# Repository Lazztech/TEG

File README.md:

# TEG — Thermal Energy Harvesting Prototype

Electronics for a thermal energy harvesting prototype: a small TEG array feeds a
sub-1 V energy-harvesting front-end (BQ25504), which charges a buffer capacitor and backs
up a regulated 5 V rail for a Noctua 5 V PWM fan and a test load.

Originally drafted on **Flux.ai**; this repo is the **KiCad** continuation, prepared for
**JLCPCB — made and assembled**.

> **Status: the sub-watt board is complete, routed, DRC-clean and orderable — but it is now a
> REFERENCE, not the deliverable.** [REQUIREMENTS.md](REQUIREMENTS.md) re-scopes the project to a
> **fireplace-mounted, wedge-shaped harvester producing ~3–4 W** with USB-A and USB-C output. At
> ~3–4 W the BQ25504 (max input power ≤ 300 mW) cannot be used, so a new power board is in design.

## Decisions made (and why)

Settled — nothing here needs your input.

| Question | Decision | Why |
|----------|----------|-----|
| **Storage: battery or supercap?** | **Neither** — a **1000 µF electrolytic buffer** (option D) | JLCPCB stocks **no** supercapacitors and no batteries (verified against their API), so those can't be machine-assembled. An electrolytic keeps the board **100 % JLCPCB-assembled**. Trade-off accepted: ≈5 mJ stored, so the **fan runs only on live harvest**, not from storage |
| **MPPT?** | **Yes — built into the BQ25504** | Sample-and-hold MPPT in hardware; no extra IC, no firmware |
| **MPPT ratio** | **≈50 % of Voc** (`R13` = `R14` = 10 MΩ) | A TEG makes maximum power at a matched load, ≈50 % of its open-circuit voltage. The datasheet's 78 % default is tuned for *solar* |
| **Voltage window** | **VBAT_OV 3.15 V** (datasheet-verified) | Conservative and tested. Protects the part; tune later if you want more usable energy |
| **Charge cutoff** | `OT_PROG` → GND = **65 °C** | Sensible protection for a device that is warm by design |
| **`VBAT_OK`** | Left unconnected (no-connect marker) | With no real energy store, gating the load buys little. Wiring it to the MT3608 `EN` is the natural upgrade if you later add a supercap |

## Remaining tasks — from here to a working prototype

| # | Task | Notes |
|---|------|-------|
| 1 | ~~Route the copper~~ | **Done** — FreeRouting, 0 DRC violations |
| 2 | ~~Export fab files~~ | **Done** — gerbers, drill, position, BOM in `build/fab/` (verify CPL rotations) |
| 3 | **Review and order** | Read `build/fab/TEG-routed.pdf` and confirm the layout; then order from JLCPCB. ⚠️ `U1` `BQ25504RGTT` stock is only **7** — `C2876746` is the same part if it sells out |
| 4 | **Optional: add a GND pour** | GND is routed as traces so the board works as-is. A pour is a nice refinement — fill it in KiCad (**zones can't be filled from the CLI**) |
| 5 | **Bench-verify before trusting the TEGs** | Drive the input from a bench supply emulating the TEG (start ~1 V, low current limit); confirm the rail comes up and the fan starts |
| 6 | **Then the thermal tests** | One-module baseline, two-module comparison, five cold starts, 0.5 W load — per [PLAN.md](PLAN.md) |

## Routing — done with FreeRouting

KiCad has no autorouter, so routing uses the standard **SPECCTRA round-trip**, scripted in
[scripts/freeroute.sh](scripts/freeroute.sh):

1. KiCad (`pcbnew` python) exports the board as a **`.dsn`** — outline, pads, nets **and the
   net-class rules**.
2. **FreeRouting** (external Java autorouter) routes it and writes a **`.ses`** session file.
3. KiCad imports the `.ses` back onto the board.
4. `kicad-cli` DRC verifies the result.

FreeRouting reported *0 unrouted, 0 violations* on both its routing and optimisation passes,
and KiCad's own DRC agrees: **0 violations, 0 unconnected**. (It also does the rip-up-and-retry
that a naive router can't — an earlier hand-written script in `scripts/route_board.py` reached
~95 % but never clean, so it was abandoned; it's kept for reference.)

### Net classes

Set in [scripts/gen_board.py](scripts/gen_board.py) and exported into the DSN so the router
obeys them:

| Class | Nets | Track | Clearance | Via |
|-------|------|-------|-----------|-----|
| Default | all signals | 0.20 mm | 0.20 mm | 0.6/0.3 |
| Power | `GND`, `+5V`, `VSTOR`, `VBAT`, `TEG+`, `TEG-` | 0.20 mm | 0.20 mm | 0.6/0.3 |

**Why not wider power traces?** Net classes are per-*net*, and the power/GND nets also land on
U1's 0.5 mm-pitch pins, where a wider track cannot escape (0.3 mm already collides with
neighbours) and the autorouter will not taper. At tens of mA, 0.2 mm is electrically ample.
The classes still exist so wider widths can be set later, after a manual fanout from U1.

## Fabrication outputs

Generated into `build/fab/` (gitignored) by **[scripts/fab_export.sh](scripts/fab_export.sh)**
— one command for the whole JLCPCB package (Gerbers + drill + BOM + CPL). Full flow and
the ordering/approval path: **[docs/jlcpcb-fabrication.md](docs/jlcpcb-fabrication.md)**.

| File | What |
|------|------|
| `TEG-gerbers.zip` | JLCPCB PCB upload — Gerbers + drill + `.gbrjob` |
| `TEG-*.gbl/.gtl/.gbs/.gts/.gbo/.gto/.gm1` + `TEG-job.gbrjob` | Gerbers (2 copper, 2 mask, 2 silk, edge) |
| `TEG.drl` | Excellon drill |
| `TEG-pos.csv` | Raw pick-and-place (`kicad-cli pcb export pos`) |
| `TEG-CPL-jlcpcb.csv` | JLCPCB **CPL** — `Designator,Val,Package,Mid X,Mid Y,Rotation,Layer` |
| `TEG-BOM-jlcpcb.csv` | JLCPCB BOM — `Comment,Designator,Footprint,LCSC Part #` |
| `TEG-routed.pdf`, `TEG-schematic.pdf` | 2D renders for review (copper visible here) |
| `build/render/TEG-*.png` | **3D renders** (top / isometric / bottom / harvester close-up) — see [scripts/render.sh](scripts/render.sh) |

⚠️ **Check the CPL rotations before ordering.** Position-file rotation conventions are a classic
source of misplacement; compare `TEG-pos.csv` against KiCad's **Fabrication Toolkit** output (or
JLCPCB's plugin) rather than trusting it blind.

## Storage — what option D means

The BQ25504 needs some reservoir on `VBAT` (the datasheet's own reference shows ">100 µF"),
and a **1000 µF 6.3 V SMD electrolytic (`C970711`)** satisfies that: it holds the rail steady
and is placed by JLCPCB.

But it stores **≈5 mJ**, against ≈1.2 J for a supercapacitor. So:

- **The fan cannot run from storage** — it turns only while the TEG array supplies enough power
  directly (high ΔT). That is arguably the most *informative* first-prototype behaviour, but
  "fan runs for a few seconds off stored energy" is **not** a capability of this build.
- ⚠️ The electrolytic is **polarised**: pin 1 = +. **Verify against the footprint silkscreen.**

If you later want real storage, it's a one-part change: add a 0.22–0.47 F / 5.5 V supercap in
place of `C2` (hand-solder or via a 2-pin header), and optionally gate the MT3608 `EN` from
`VBAT_OK`. The threshold network already suits a 5.5 V cell.

## Parts — all verified in the JLCPCB catalogue

Sourced with [scripts/jlc_lookup.py](scripts/jlc_lookup.py) (JLCPCB's own parts API: id,
library type, stock). Highlights:

| Ref | Part | LCSC | Stock |
|-----|------|------|-------|
| `U1` | BQ25504RGTT (harvester + MPPT) | C157471 | ⚠️ 7 (alt `C2876746` = 21) |
| `U2` | MT3608 (5 V boost) | C84817 | 129 k |
| `Q1` / `D1`,`D2` | AO3400A / 1N5819WS | C20917 / C191023 | base parts |
| `L1`,`L2` | 22 µH `SWPA4020S220MT` | C82401 | 6 007 |
| `C2` | 1000 µF 6.3 V electrolytic | C970711 | 1 888 |
| `R1`/`R2`/`R3`/`R4`+`R15`/`R7`/`R6` | 5.90 / 4.02 / 5.60 / 4.42 / 4.22 / 1.43 MΩ | C2076902 / C137708 / C23190 / C166806 / C166807 / C166898 | 775 – 58 k |
| `R8` / `R9` | 73.2 kΩ / 10 kΩ (MT3608 → **5.0 V**) | C2933257 / C25804 | ok |
| `R10` / `R13`,`R14` | 1 kΩ / 10 MΩ | C21190 / C114606 | ok |
| `J1`,`J3` / `J2` | KF128 screw terminal / 4-pin fan header | C474952 / C2691448 | ok |

## Connectors & wiring

| Ref | Type | Pins | Purpose |
|-----|------|------|---------|
| **J1** | 2-pos screw terminal (`KF128-5.08-2P`) | 1: `TEG+`, 2: `TEG-` | **TEG array input** |
| **J2** | 4-pin header, 2.54 mm | 1: `GND`, 2: `+5V`, 3: `FAN_TACH`, 4: `FAN_PWM` | Noctua fan |
| **J3** | 2-pos screw terminal (`KF128-5.08-2P`) | 1: `LOAD_SW` (switched), 2: `+5V` | 5 V test load, switched by Q1 |

### Wiring two TEGs in series (current 2-position J1)

```
TEG A(-) ──┬── TEG B(+)          # series junction, made off-board in the wiring
           │
TEG A(+) ──┴── J1 pin 1  (TEG+)
TEG B(-) ────── J1 pin 2  (TEG-)
```

**Series doubles the voltage and leaves the current unchanged** — which is what you want at
low ΔT, where each module produces only a fraction of a volt. Parallel would double the current
at the same low voltage instead.

⚠️ **Limitation of the 2-position terminal:** the series junction is made in the wiring, so the
two modules **cannot be measured independently at the board**, and running the one-module
baseline means rewiring the string. The plan asks to keep module leads accessible for
independent measurement. A **3-position** terminal (`KF128-5.08-3P`, LCSC `C474953`, in stock)
would bring the midpoint onto the board — `TEG_A+`, `midpoint`, `TEG_B-` — making each module
meterable and the baseline a no-rewire change. Roughly 5 mm wider, so it needs a placement
nudge and a reroute.

### Fan

There is **no MCU on the board**, so `FAN_PWM` (J2 pin 4) must be driven by an external source —
a bench supply, signal generator, or your instrumentation. `FAN_TACH` (pin 3) has a 10 kΩ
pull-up to `+5V` (R11) so you can read fan speed. Feed the fan from `+5V` (pin 2) and `GND` (pin 1).

## Continuous validation

Every pull request runs these checks (see **[docs/validation.md](docs/validation.md)**):

| Check | What it proves |
|-------|----------------|
| **CAD artifacts** | Rebuilds the build123d wedge and requires the committed STEP/STL to match. Every STL is a closed, single-body, bed-fitting mesh. |
| **ERC / DRC** | `kicad-cli` (KiCad 10) finds no error-level schematic or board violations. |
| **Fab package** | Gerbers, drill, CPL, BOM and the JLCPCB zip build; nothing is ordered. |
| **Scripts** | All shell scripts parse and all Python sources compile. |

Run the same checks locally with `scripts/validate.sh` (add `--cad` if KiCad is
not installed). A failing CAD check usually means the committed exports are
stale: run `scripts/cad-run.sh` and commit the updated artifacts.

## What to expect when you test

**Two TG12-4 modules produce only a few hundred mW at useful ΔT, while the fan draws
~0.5 W.** With option D there is no energy store, so the fan will turn **only while ΔT is
high enough** — it will not run continuously, and it will not run from stored energy. That is
the expected behaviour of this build, not a fault.

## Repo layout

| Path | What it is |
|------|------------|
| [REQUIREMENTS.md](REQUIREMENTS.md) | **Whole-device requirements** — electrical, mechanical, thermal/safety, manufacturing, and the system BOM split into *from JLCPCB* vs *buy separately* |
| [BOM.md](BOM.md) | Board bill of materials (the sub-watt reference design) |
| [PLAN.md](PLAN.md) | Living plan: findings, decisions, open questions, changelog |
| [docs/validation.md](docs/validation.md) | **CI + local validation flow** — what every push checks, how to fix a failing artifact |
| [.github/workflows/validate.yml](.github/workflows/validate.yml) | CI: rebuild/validate CAD, lint/test the model code, run KiCad ERC/DRC, syntax-check scripts |
| [docs/jlcpcb-fabrication.md](docs/jlcpcb-fabrication.md) | **End-to-end JLCPCB flow** — fab package command, verification checklist, manual approval-gated ordering |
| `hardware/TEG.kicad_pro` | KiCad project |
| `hardware/TEG.kicad_sch` | Root schematic (auto-generated — nets defined by pin labels) |
| `hardware/TEG.kicad_pcb` | Board (auto-generated — 33 footprints placed and netted, **no copper routed yet**) |
| `hardware/libs/TEG.kicad_sym` | Project symbol library (`TEG:`) |
| `hardware/footprints/TEG.pretty/` | Project footprint library (`TEG:`) |
| `hardware/easyeda2kicad.3dshapes/` | 3D WRL models, named as the footprints reference them |
| `scripts/gen_schematic.py` | Regenerates `TEG.kicad_sch` from the part/net table inside it |
| `scripts/gen_board.py` | Regenerates `TEG.kicad_pcb` (shares the netlist with `gen_schematic.py`) |
| `scripts/validate.sh` | **All checks**: rebuild/validate the code-CAD exports, then KiCad ERC + DRC (`--cad` / `--hardware` for one half) |
| `scripts/validate_cad.py` | Validates committed CAD STEP/STL artifacts: manifold mesh, bed fit, STEP↔STL agreement, stale-export check |
| `scripts/jlc_lookup.py` | Queries JLCPCB's own parts API — id, library type, stock |
| `scripts/fab_export.sh` | **One command** → JLCPCB package (Gerbers + drill + BOM + CPL) in `build/fab/` |
| `scripts/jlc_bom.py` | Schematic → JLCPCB BOM CSV (`Comment,Designator,Footprint,LCSC Part #`) |
| `scripts/jlc_cpl.py` | KiCad `pos` CSV → JLCPCB CPL CSV |
| `scripts/freeroute.sh` | Routes the board via the SPECCTRA DSN→FreeRouting→SES round-trip, then DRCs |
| `scripts/render.sh` | Renders 3D views of the board (with component bodies) into `build/render/` |
| `scripts/route_board.py` | *Abandoned* hand-written router (kept for reference; not used) |

## Opening the project

Open `hardware/TEG.kicad_pro` in **KiCad 7 or 8** (developed with KiCad 10). The library
tables are already set up, so all parts appear under the `TEG:` nickname.

The schematic and board are **generated** — edit the part/net table in
`scripts/gen_schematic.py` (and placements in `scripts/gen_board.py`) and re-run:

```bash
python3 scripts/gen_schematic.py   # -> hardware/TEG.kicad_sch
python3 scripts/gen_board.py       # -> hardware/TEG.kicad_pcb (unrouted, wipes routing)
./scripts/freeroute.sh             # route it (DSN -> FreeRouting -> SES -> DRC)
./scripts/validate.sh              # all checks (CAD artifacts + ERC/DRC)
./scripts/validate.sh --cad        # CAD artifacts only, no KiCad needed
python3 scripts/jlc_lookup.py "22uH inductor"   # search the JLCPCB catalogue

# one-command JLCPCB package: gerbers + drill + BOM + CPL into build/fab/
scripts/fab_export.sh              # see docs/jlcpcb-fabrication.md (ordering is manual + approval-gated)
```

**Known cosmetic warnings** (safe to ignore): ERC reports 3 × `lib_symbol_mismatch` on the two
most recently fetched symbols (their embedded text is byte-identical to the library — an
unresolved KiCad quirk), and DRC reports 1 × `silk_overlap` where the 8 mm electrolytic's
reference text crosses its own silkscreen. Neither affects fabrication.

## Tooling — JLCPCB parts

Two tools, for different jobs:

- **`scripts/jlc_lookup.py`** — *finding* parts. Queries JLCPCB's own API and returns id,
  library type (`base` = no setup fee / `expand` = extended) and stock.
- **`jlc-client`** — *fetching* a part's KiCad symbol/footprint/3D model by LCSC id, and
  appending symbols to the project library:

```bash
# Fetch symbol + footprint + 3D and append the symbol to the project library
JLC_API_TOKEN='<token>' jlc-client --symbol -l ./hardware/libs/TEG.kicad_sym \
    --footprint --footprint-lib TEG -o ./hardware/footprints C157471 C84817
```

Caveats learned the hard way (see [PLAN.md](PLAN.md) §3):

- `jlc-client`'s **search** is unreliable — as of 2026-10-10 it returns the same high-stock
  list for *every* query. Use `jlc_lookup.py` to search and `jlc-client` to fetch by id.
- `jlc-client search --type ic` also filters to one subcategory and hides power ICs.
- The component **fetch** endpoint is intermittent (`Component … not found on EasyEDA/LCSC`
  for everything, then recovers). Retry.

## Design in one paragraph

Two Marlow TG12-4-01LS TEG modules in series feed the BQ25504 boost charger through a screw
terminal. The BQ25504 does **MPPT in hardware**: `R13`/`R14` sample a fraction of the
harvester's open-circuit voltage onto a hold cap, and the chip regulates its input to that
fraction — set to **≈50 % of Voc**, matched-load MPP for a TEG. The charger holds a 1000 µF
electrolytic buffer on `VBAT` and exposes `VSTOR`; an MT3608 boost then regulates a 5 V rail
for the Noctua NF-A8 4-pin PWM fan (Tach pull-up, PWM from a test header) and a switchable
0.5 W test load (AO3400A low-side MOSFET). Two-stage on purpose: it keeps the harvester's MPPT
decoupled from load transients and lets the buffer stabilise before the 5 V boost is asked to run.

Open questions and thermal/mechanical context: [PLAN.md](PLAN.md).

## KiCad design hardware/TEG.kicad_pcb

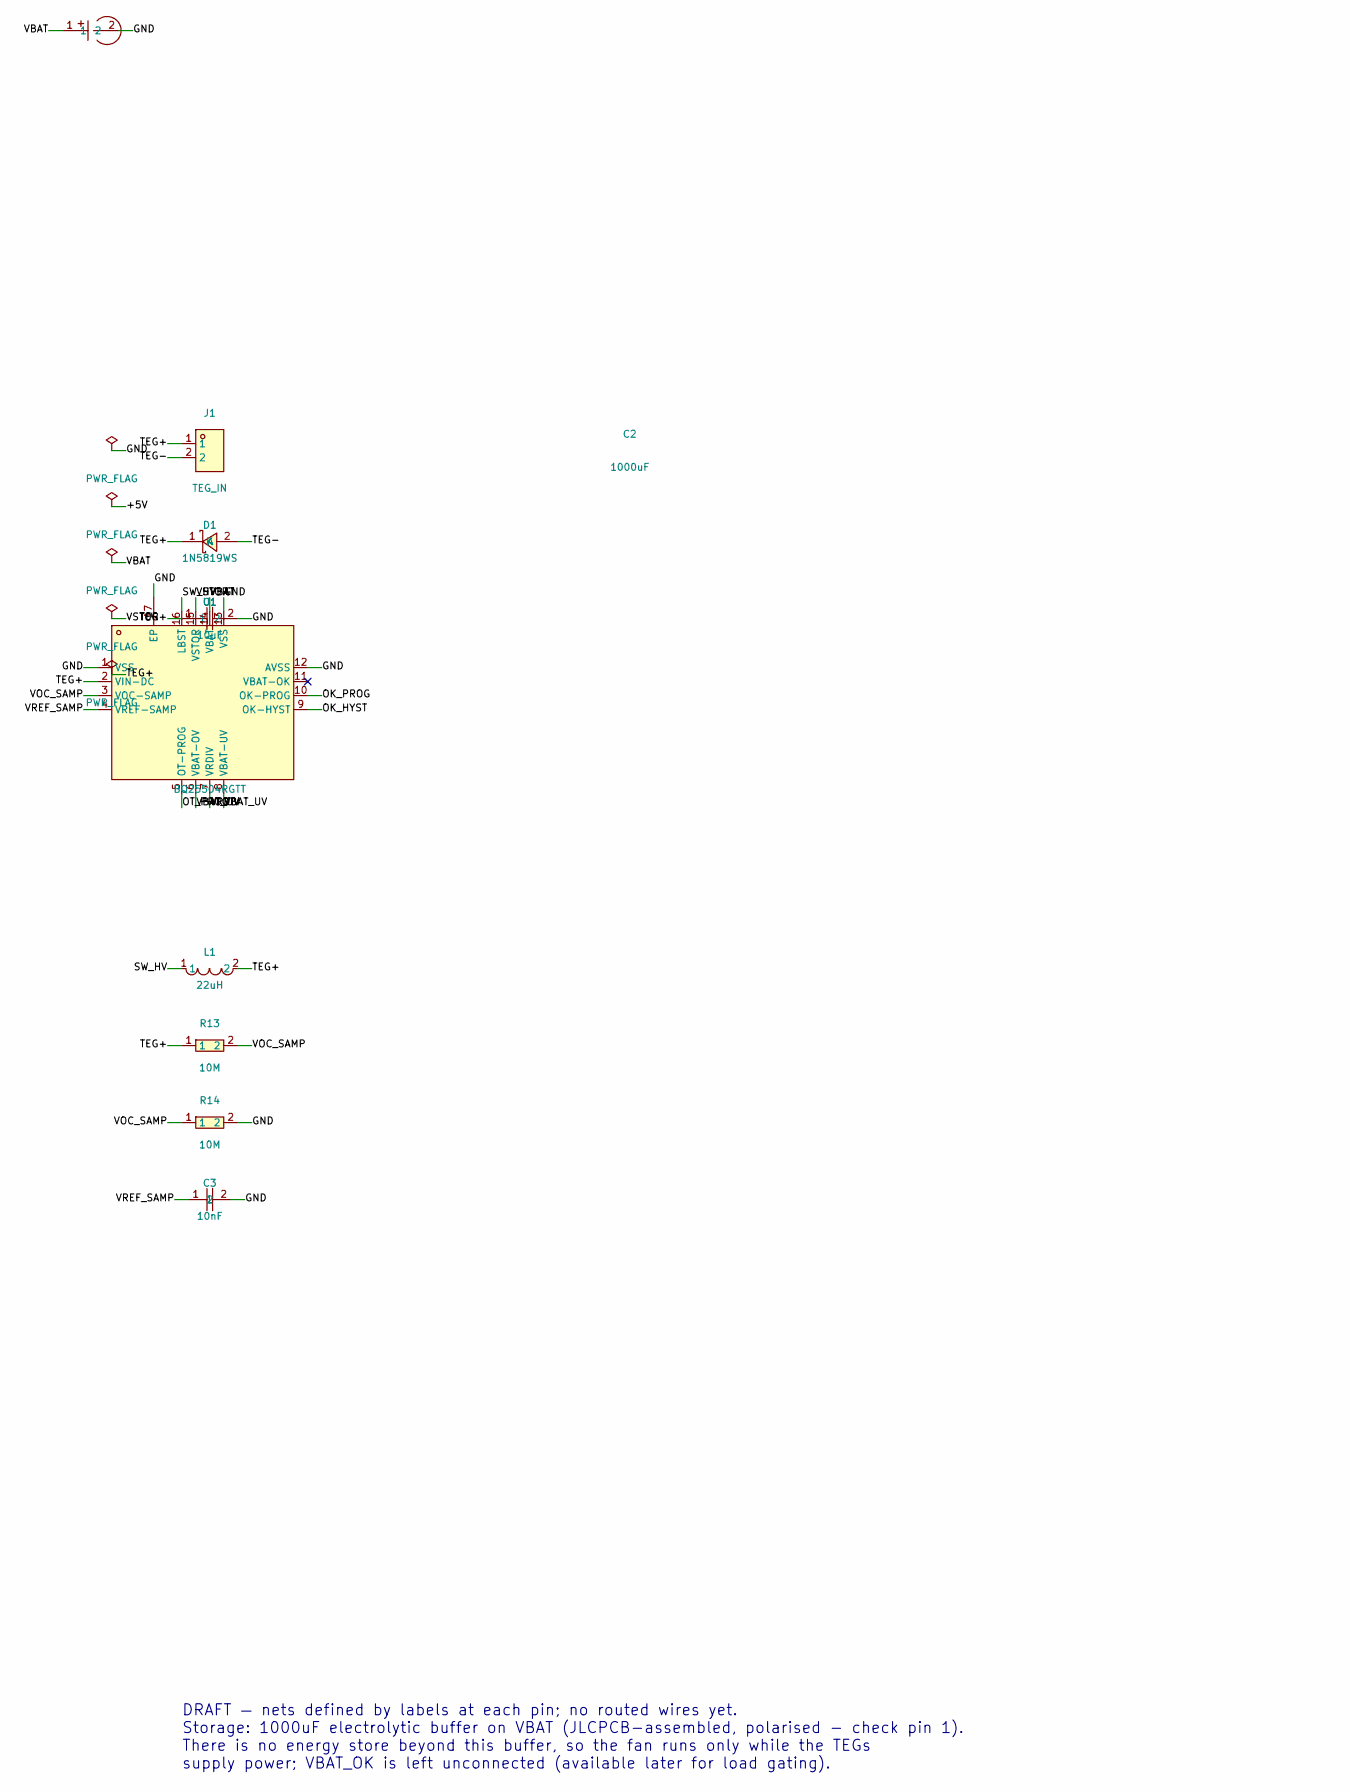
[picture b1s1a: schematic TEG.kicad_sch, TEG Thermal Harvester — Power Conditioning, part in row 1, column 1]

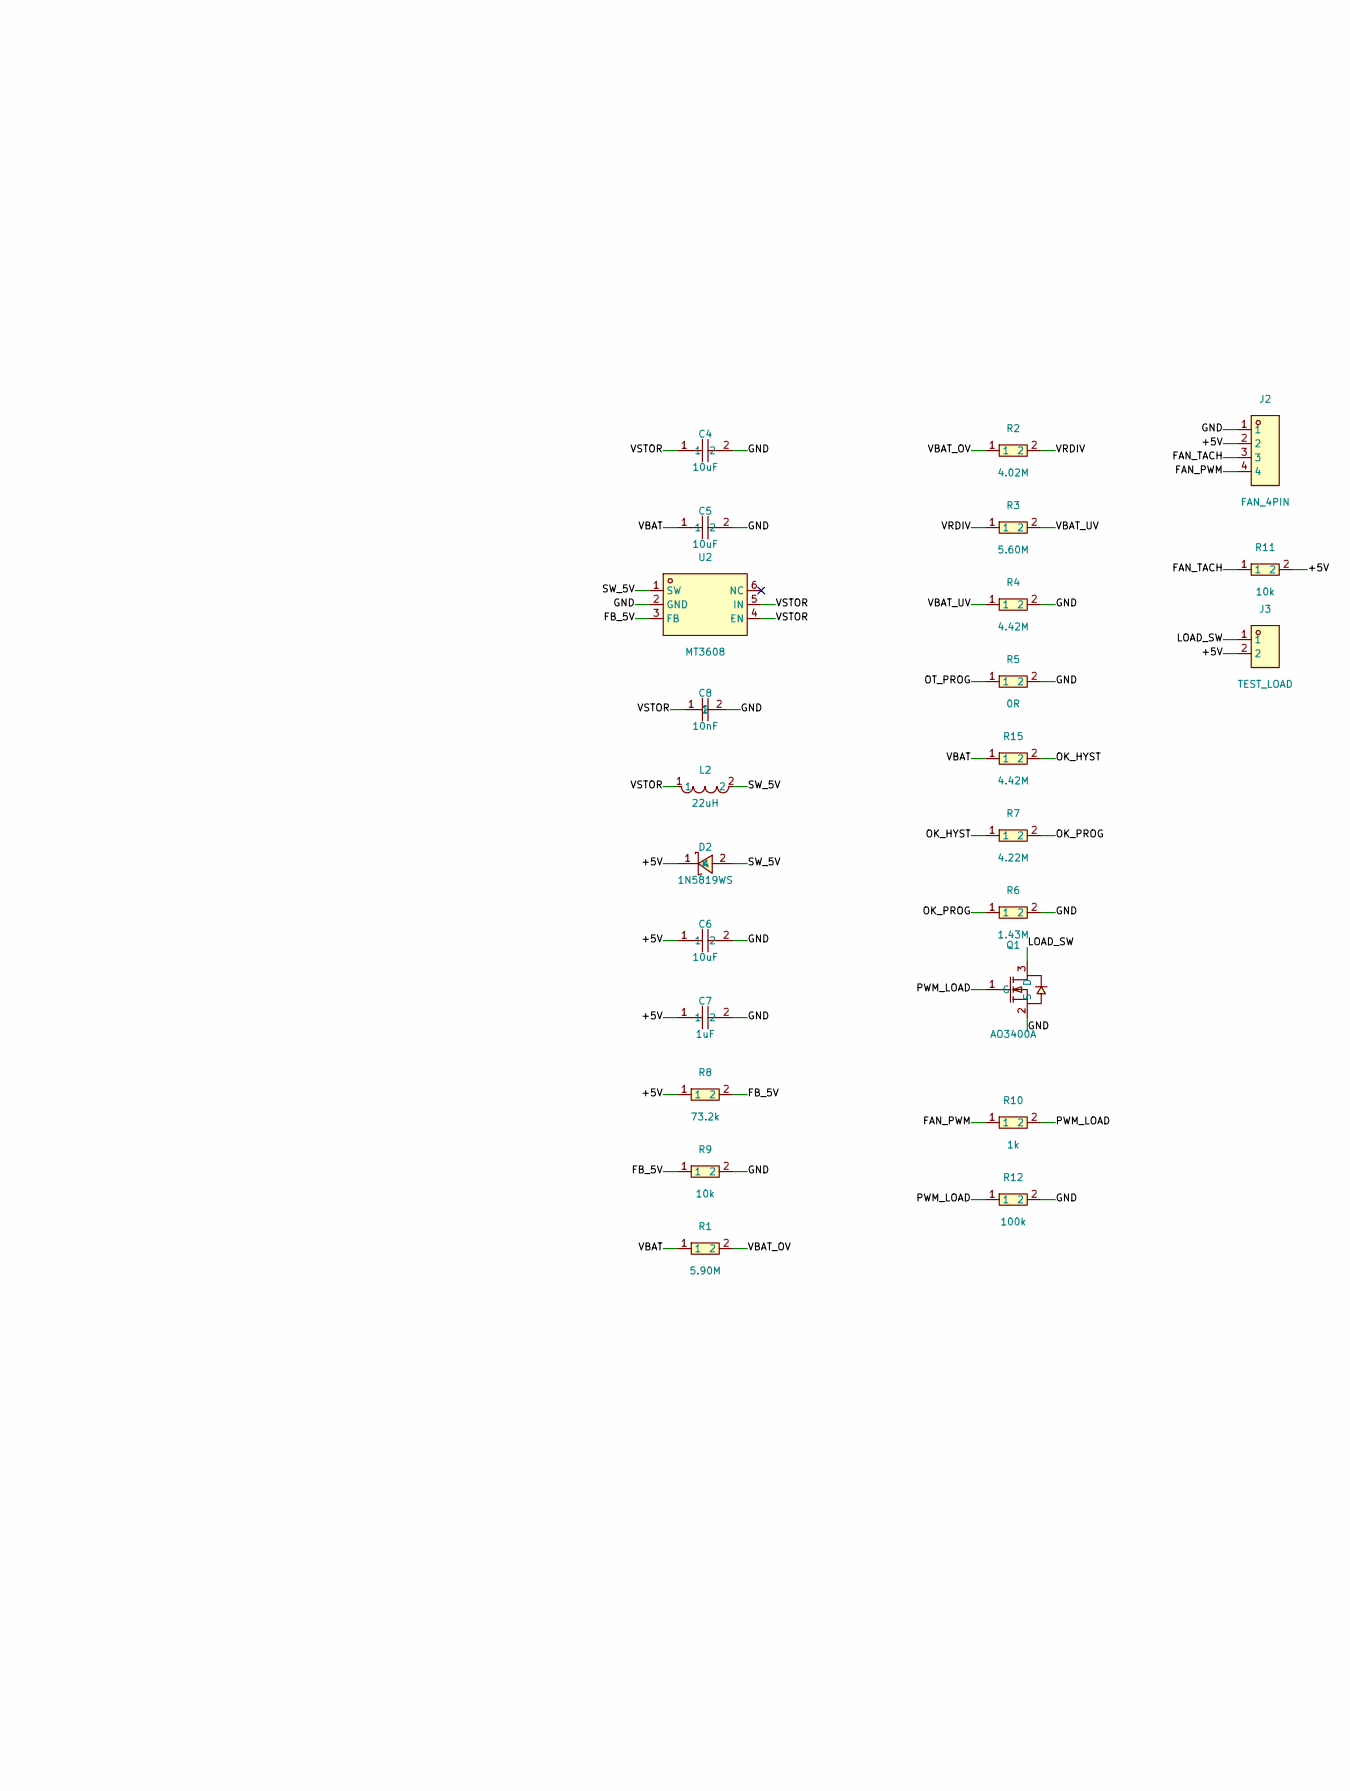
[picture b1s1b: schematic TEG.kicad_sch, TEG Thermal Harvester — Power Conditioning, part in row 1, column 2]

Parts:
C1, C4, C5, C6: 10uF; C0805; LCSC Part C15850
C2: 1000uF; CAP-SMD_BD8.0-L8.3-W8.3-LS9.3-FD-1; LCSC Part C970711
C3, C8: 10nF; C0603; LCSC Part C1589
C7: 1uF; C0603; LCSC Part C15849
D1, D2: 1N5819WS; SOD-323_L1.8-W1.3-LS2.5-RD; LCSC Part C191023
J1: TEG_IN; CONN-TH_P5.08_KF128-5.08-2P; LCSC Part C474952
J2: FAN_4PIN; HDR-TH_4P-P2.54-V-M; LCSC Part C2691448
J3: TEST_LOAD; CONN-TH_P5.08_KF128-5.08-2P; LCSC Part C474952
L1, L2: 22uH; IND-SMD_L4.0-W4.0; LCSC Part C82401
Q1: AO3400A; SOT-23-3_L2.9-W1.3-P1.90-LS2.4-BR; LCSC Part C20917
R1: 5.90M; R0603; LCSC Part C2076902
R2: 4.02M; R0603; LCSC Part C137708
R3: 5.60M; R0603; LCSC Part C23190
R4, R15: 4.42M; R0603; LCSC Part C166806
R5: 0R; R0603; LCSC Part C21189
R6: 1.43M; R0603; LCSC Part C166898
R7: 4.22M; R0603; LCSC Part C166807
R8: 73.2k; R0603; LCSC Part C2933257
R9, R11: 10k; R0603; LCSC Part C25804
R10: 1k; R0603; LCSC Part C21190
R12: 100k; R0603; LCSC Part C25803
R13, R14: 10M; R0603; LCSC Part C114606
U1: BQ25504RGTT; VQFN-16_L3.0-W3.0-P0.50-TL-EP; LCSC Part C157471
U2: MT3608; SOT-23-6_L2.9-W1.6-P0.95-LS2.8-BL; LCSC Part C84817

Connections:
+5V: C6.1, C7.1, D2.1 (K), J2.2, J3.2, R8.1, R11.2
FAN_PWM: J2.4, R10.1
FAN_TACH: J2.3, R11.1
FB_5V: R8.2, R9.1, U2.3 (FB)
GND: C1.2, C2.2, C3.2, C4.2, C5.2, C6.2, C7.2, C8.2, J2.1, Q1.2 (S), R4.2, R5.2, R6.2, R9.2, R12.2, R14.2, U1.1 (VSS), U1.12 (AVSS), U1.13 (VSS), U1.17 (EP), U2.2 (GND)
LOAD_SW: J3.1, Q1.3 (D)
OK_HYST: R7.1, R15.2, U1.9 (OK-HYST)
OK_PROG: R6.1, R7.2, U1.10 (OK-PROG)
OT_PROG: R5.1, U1.5 (OT-PROG)
PWM_LOAD: Q1.1 (G), R10.2, R12.1
SW_5V: D2.2 (A), L2.2, U2.1 (SW)
SW_HV: L1.1, U1.16 (LBST)
TEG+: C1.1, D1.1 (K), J1.1, L1.2, R13.1, U1.2 (VIN-DC)
TEG-: D1.2 (A), J1.2
VBAT: C2.1, C5.1, R1.1, R15.1, U1.14 (VBAT)
VBAT_OV: R1.2, R2.1, U1.6 (VBAT-OV)
VBAT_UV: R3.2, R4.1, U1.8 (VBAT-UV)
VOC_SAMP: R13.2, R14.1, U1.3 (VOC-SAMP)
VRDIV: R2.2, R3.1, U1.7 (VRDIV)
VREF_SAMP: C3.1, U1.4 (VREF-SAMP)
VSTOR: C4.1, C8.1, L2.1, U1.15 (VSTOR), U2.4 (EN), U2.5 (IN)

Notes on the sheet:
DRAFT — nets defined by labels at each pin; no routed wires yet. Storage: 1000uF electrolytic buffer on VBAT (JLCPCB-assembled, polarised - check pin 1). There is no energy store beyond this buffer, so the fan runs only while the TEGs supply power; VBAT_OK is left unconnected (available later for l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

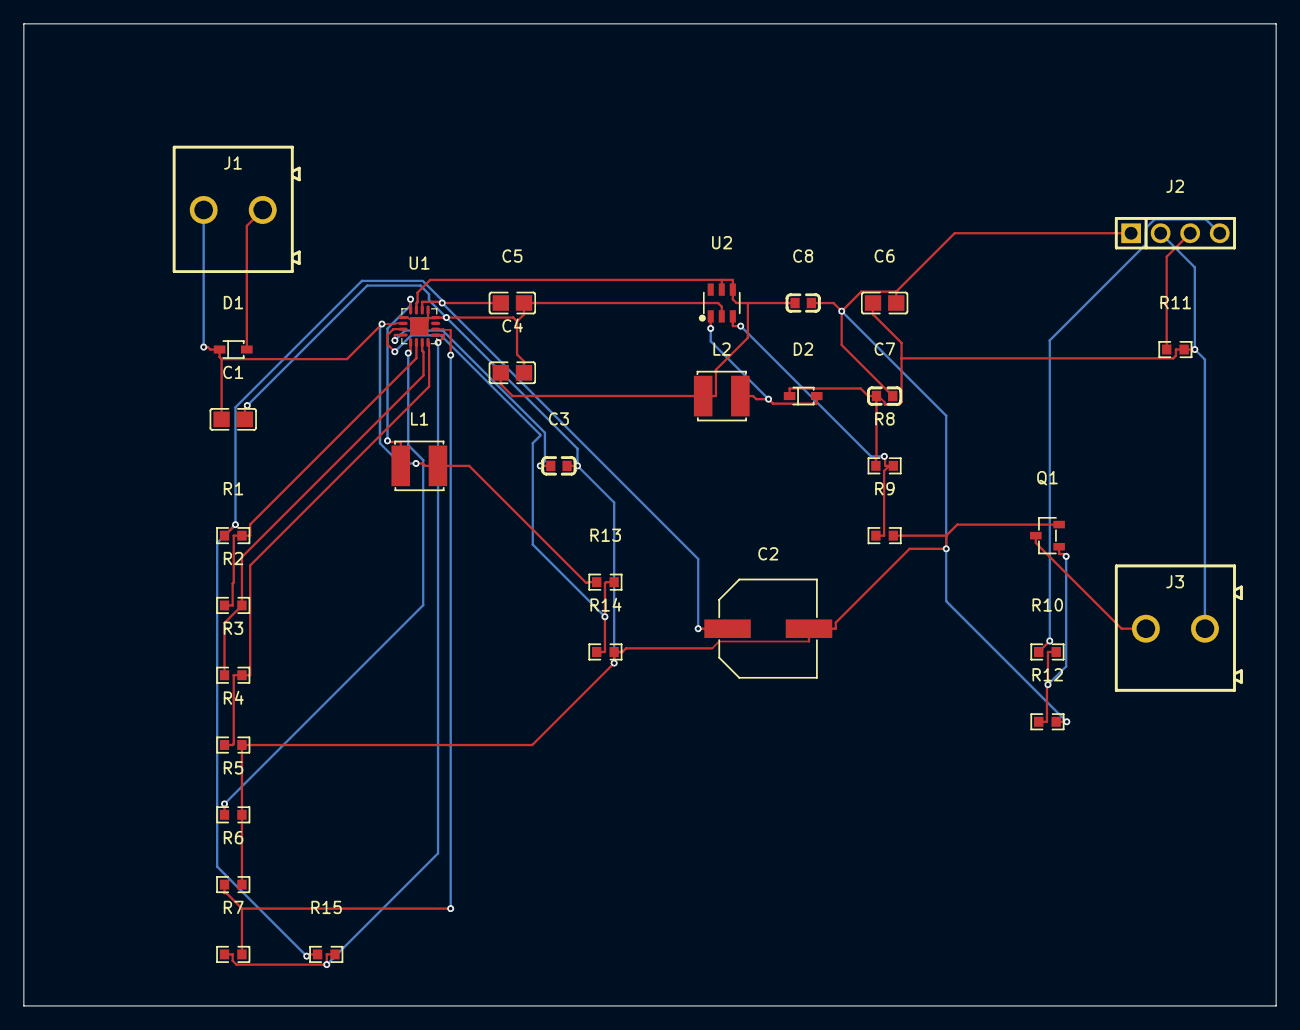
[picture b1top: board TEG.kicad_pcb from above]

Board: 2 copper layers, 107.7 x 84.4 mm, 33 parts (0 on the bottom side), 21 nets.
